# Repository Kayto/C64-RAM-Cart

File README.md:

# C64 RAM Cartridge

## Latest News

Please note this PCB remains untested so please review and understand the risk in proceeding.
I do hope to pick up in 2024 so watch this space.

## Background

C64 Cartridges were convenient and easy to use. Programs on cartridge loaded instantly. Typically cartridges used EPROMs (Erasable Programmable Read-Only Memories). The only downside of ROM was the inconvenience of making quick changes with the need for a seperate EPROM burner and an eraser. Contemporary articles note that EPROMS were relatively expensive at $25 each and the need for a burner and eraser equating to around $200.
As RAM became cheaper (at nearer $15 each) at the end of the 1980s, RAM based storage devices became more prevalent for the C64 with products such as the RAMLINK and GeoRAM cartridges finding use. Additional offerings were produced and hobbyist examples published such as the RAM cart presented here. Given the general developments in computing at this time, usage and adoption was rather limited by the availability of software towards the end of the 8 bit era. 

## Introduction
This C64 RAM cartridge is a recreation of the Super Luxus CMOS RAM Platine from the 64'er magazine dated March 1989. It provides 256Kb of battery backed RAM instead of the usual memory expansion provided by EPROMS. Put simply it acts as a RAM disc for the storage of data in conjunction with the program provided on an onboard EPROM. 

## Credit 

We should start with the credit, as this board was designed and created by J Schucht. The design files are offered for educational purposes only.
Thanks also due for [TEBL](https://github.com/tebl/C64-BlinkenDiag) and any associated credits for some of the KiCad items.

## Aims
My motivation for this recreation is as an electronics hobbyist and C64 fan - to improve KiCad, hardware workings and generally coding.

## The PCBs

KiCad, Schematics and Gerbers are provided. Renders of the boards are shown in the KiCad directory. Please review before making a commitment. No warranties or support are provided. As of this date the designs remain untested.

## The Code

The EPROM code containing the program for usage is avaiable on the associated 64'er disc. This is currently available from [archive.org](https://archive.org/download/64er_Magazin_89-03_1989_Markt_Technik_de_Side_A)

The control software (listing) is published in packed form, once the listing with the MSE has been entered and saved, the program "RAM-Platine.pac" must be loaded with "'8" and started with RUN. Two files are now created on the previously inserted floppy disk: "RAM PLATlNE 4.2" and "RAM RW $c 0000 4.2". 
The program "RAMPLATlNE4.2" is the control software to be burned into a 2764 EPROM. The second program allows you to read and write to the CMOS RAM without activating the control EPROM.

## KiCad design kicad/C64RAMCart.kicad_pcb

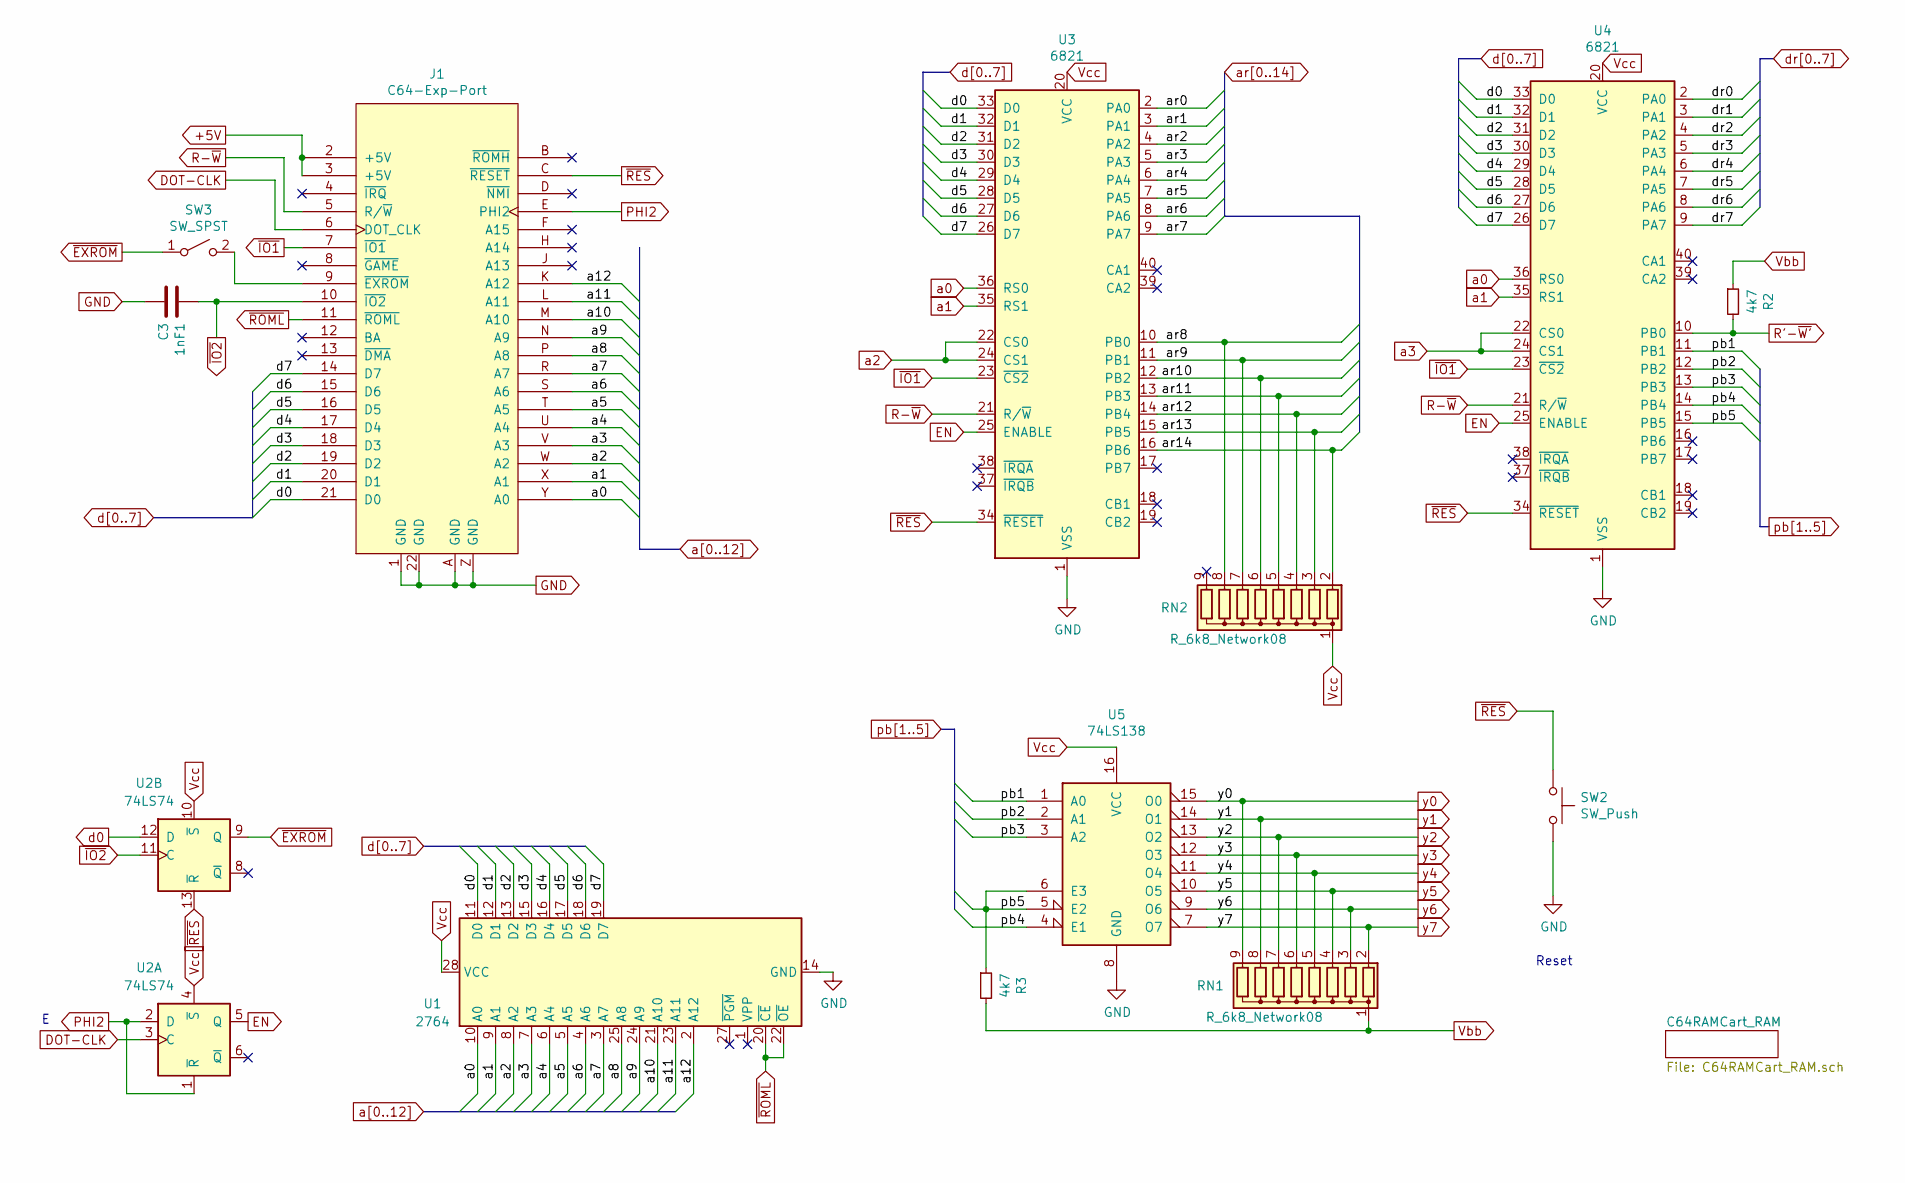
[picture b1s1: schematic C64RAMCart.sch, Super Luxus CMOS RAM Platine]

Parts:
1nF1: C3; C_Disc_D4.3mm_W1.9mm_P5.00mm
J1: C64-Exp-Port; C64_Expansion_Port
R2, R3: 4k7; R_Axial_DIN0207_L6.3mm_D2.5mm_P7.62mm_Horizontal
RN1, RN2: R_6k8_Network08; R_Array_SIP9
SW2: SW_Push; SW_PUSH_6mm_H7.3mm
SW3: SW_SPST; PinHeader_1x03_P2.54mm_Vertical
U1: 2764; DIP-28_W15.24mm_Socket
U2: 74LS74; DIP-14_W7.62mm_Socket
U3, U4: 6821; DIP-40_W15.24mm_Socket
U5: 74LS138; DIP-16_W7.62mm_Socket

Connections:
+5V: J1.2 (+5V), J1.3 (+5V), RN2.1 (common), U1.28 (VCC), U2.4 (~S), U2.10 (~S), U3.20 (VCC), U4.20 (VCC), U5.16 (VCC); also elsewhere on the board
BVcc: R2.1, R3.2, RN1.1 (common); also elsewhere on the board
DOT-CLK: J1.6 (DOT_CLK), U2.3 (C)
EN: U2.5 (Q), U3.25 (ENABLE), U4.25 (ENABLE)
GND: 1nF1.2, J1.1 (GND), J1.22 (GND), J1.A (GND), J1.Z (GND), SW2.2, U1.14 (GND), U3.1 (VSS), U4.1 (VSS), U5.8 (GND); also elsewhere on the board
unnamed: J1.9 (~EXROM), SW3.2 (B)
PHI2: J1.E (PHI2), U2.1 (~R), U2.2 (D)
R'-~W': R2.2, U4.10 (PB0); also elsewhere on the board
R-~W: J1.5 (R/~W), U3.21 (R/~W), U4.21 (R/~W)
a0: J1.Y (A0), U1.10 (A0), U3.36 (RS0), U4.36 (RS0)
a1: J1.X (A1), U1.9 (A1), U3.35 (RS1), U4.35 (RS1)
a2: J1.W (A2), U1.8 (A2), U3.22 (CS0), U3.24 (CS1)
a3: J1.V (A3), U1.7 (A3), U4.22 (CS0), U4.24 (CS1)
a4: J1.U (A4), U1.6 (A4)
a5: J1.T (A5), U1.5 (A5)
a6: J1.S (A6), U1.4 (A6)
a7: J1.R (A7), U1.3 (A7)
a8: J1.P (A8), U1.25 (A8)
a9: J1.N (A9), U1.24 (A9)
a10: J1.M (A10), U1.21 (A10)
a11: J1.L (A11), U1.23 (A11)
a12: J1.K (A12), U1.2 (A12)
ar0: U3.2 (PA0); also elsewhere on the board
ar1: U3.3 (PA1); also elsewhere on the board
ar2: U3.4 (PA2); also elsewhere on the board
ar3: U3.5 (PA3); also elsewhere on the board
ar4: U3.6 (PA4); also elsewhere on the board
ar5: U3.7 (PA5); also elsewhere on the board
ar6: U3.8 (PA6); also elsewhere on the board
ar7: U3.9 (PA7); also elsewhere on the board
ar8: RN2.8 (R7), U3.10 (PB0); also elsewhere on the board
ar9: RN2.7 (R6), U3.11 (PB1); also elsewhere on the board
ar10: RN2.6 (R5), U3.12 (PB2); also elsewhere on the board
ar11: RN2.5 (R4), U3.13 (PB3); also elsewhere on the board
ar12: RN2.4 (R3), U3.14 (PB4); also elsewhere on the board
ar13: RN2.3 (R2), U3.15 (PB5); also elsewhere on the board
ar14: RN2.2 (R1), U3.16 (PB6); also elsewhere on the board
d0: J1.21 (D0), U1.11 (D0), U2.12 (D), U3.33 (D0), U4.33 (D0)
d1: J1.20 (D1), U1.12 (D1), U3.32 (D1), U4.32 (D1)
d2: J1.19 (D2), U1.13 (D2), U3.31 (D2), U4.31 (D2)
d3: J1.18 (D3), U1.15 (D3), U3.30 (D3), U4.30 (D3)
d4: J1.17 (D4), U1.16 (D4), U3.29 (D4), U4.29 (D4)
d5: J1.16 (D5), U1.17 (D5), U3.28 (D5), U4.28 (D5)
d6: J1.15 (D6), U1.18 (D6), U3.27 (D6), U4.27 (D6)
d7: J1.14 (D7), U1.19 (D7), U3.26 (D7), U4.26 (D7)
dr0: U4.2 (PA0); also elsewhere on the board
dr1: U4.3 (PA1); also elsewhere on the board
dr2: U4.4 (PA2); also elsewhere on the board
dr3: U4.5 (PA3); also elsewhere on the board
dr4: U4.6 (PA4); also elsewhere on the board
dr5: U4.7 (PA5); also elsewhere on the board
dr6: U4.8 (PA6); also elsewhere on the board
dr7: U4.9 (PA7); also elsewhere on the board
pb1: U4.11 (PB1), U5.1 (A0)
pb2: U4.12 (PB2), U5.2 (A1)
pb3: U4.13 (PB3), U5.3 (A2)
pb4: U4.14 (PB4), U5.4 (E1)
pb5: R3.1, U4.15 (PB5), U5.5 (E2), U5.6 (E3)
y0: RN1.9 (R8), U5.15 (O0); also elsewhere on the board
y1: RN1.8 (R7), U5.14 (O1); also elsewhere on the board
y2: RN1.7 (R6), U5.13 (O2); also elsewhere on the board
y3: RN1.6 (R5), U5.12 (O3); also elsewhere on the board
y4: RN1.5 (R4), U5.11 (O4); also elsewhere on the board
y5: RN1.4 (R3), U5.10 (O5); also elsewhere on the board
y6: RN1.3 (R2), U5.9 (O6); also elsewhere on the board
y7: RN1.2 (R1), U5.7 (O7); also elsewhere on the board
~EXROM: SW3.1 (A), U2.9 (Q)
~IO1: J1.7 (~IO1), U3.23 (~CS2), U4.23 (~CS2)
~IO2: 1nF1.1, J1.10 (~IO2), U2.11 (C)
~RES: J1.C (~RESET), SW2.1, U2.13 (~R), U3.34 (~RESET), U4.34 (~RESET)
~ROML: J1.11 (~ROML), U1.20 (~CE), U1.22 (~OE)

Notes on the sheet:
Reset

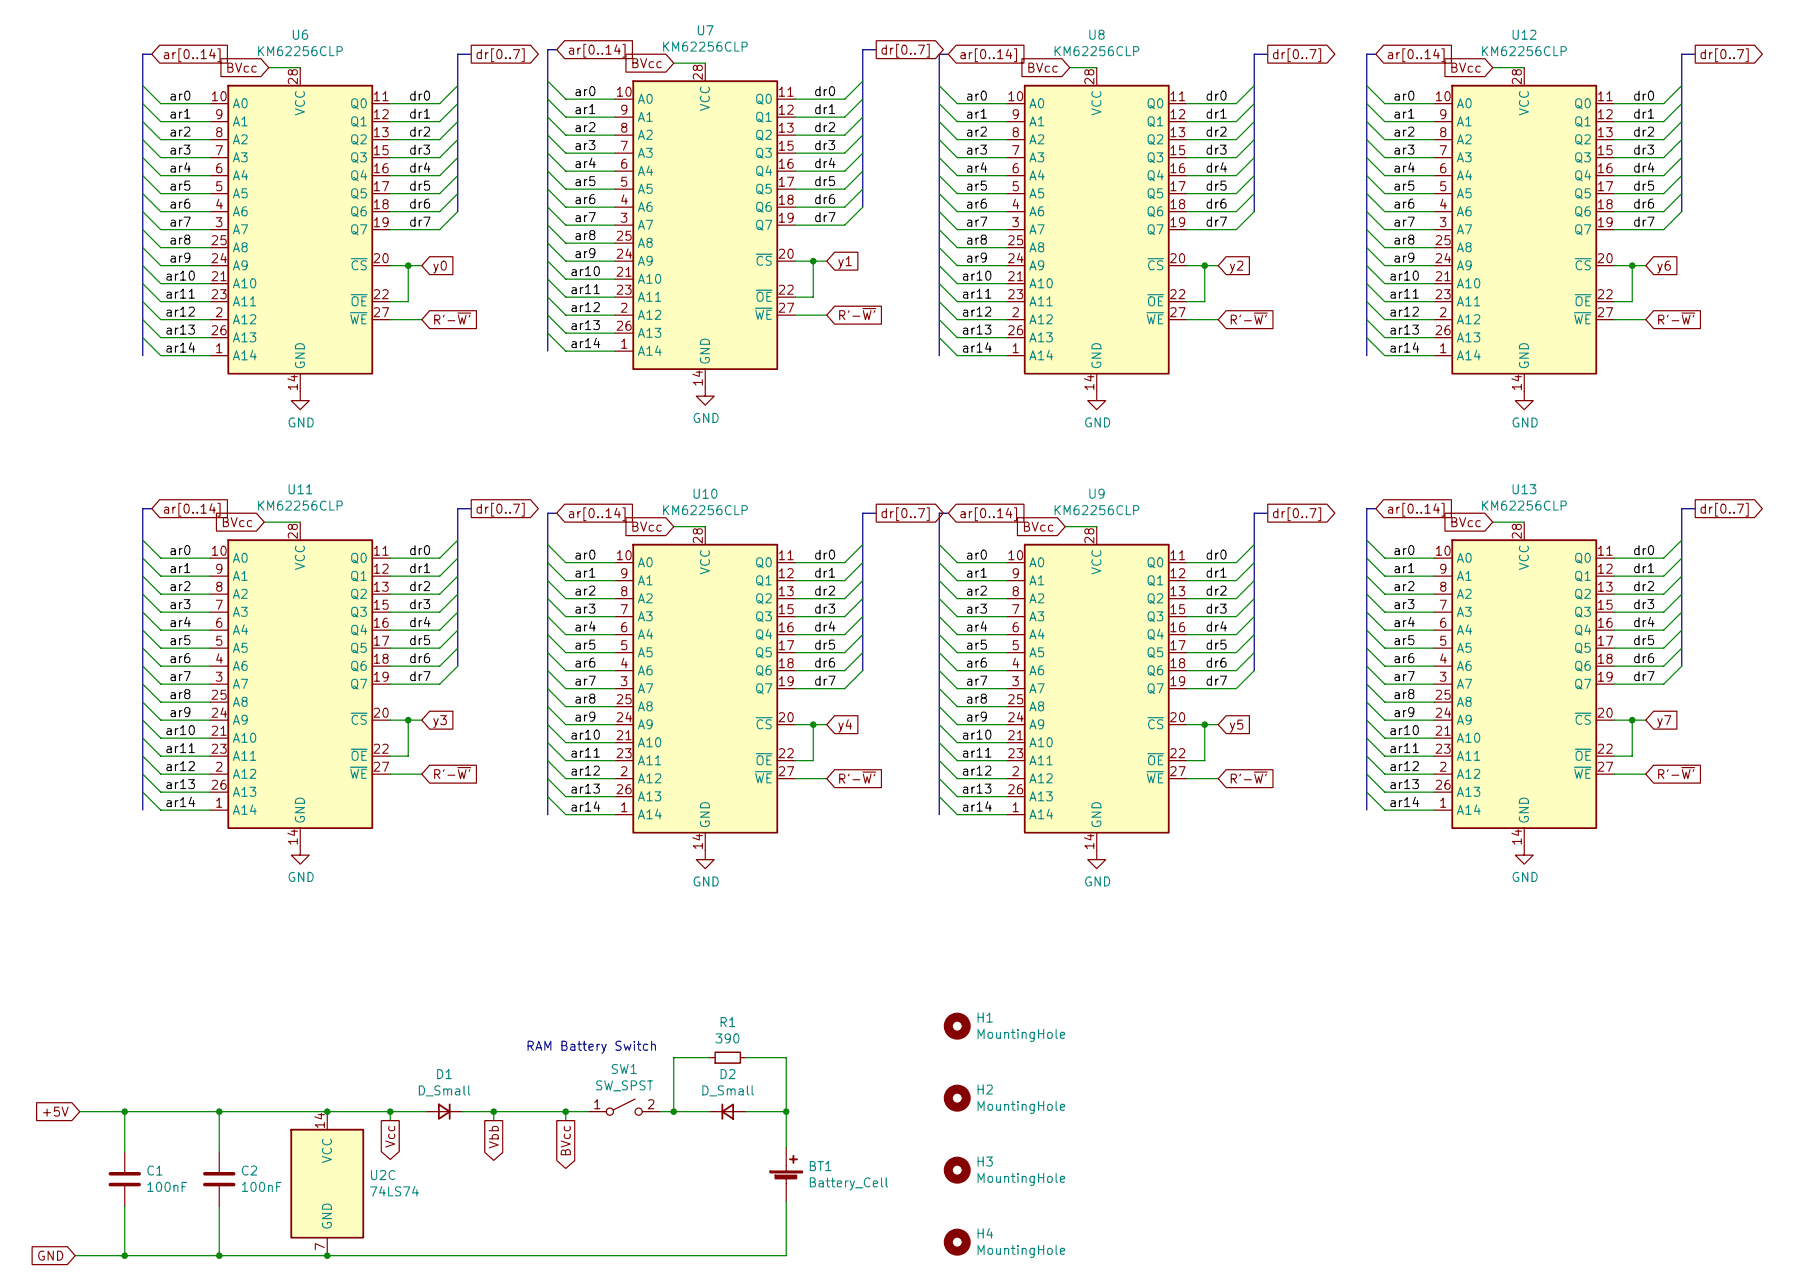
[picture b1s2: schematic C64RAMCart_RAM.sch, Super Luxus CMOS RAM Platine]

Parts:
BT1: Battery_Cell; BatteryHolder_Keystone_103_1x20mm
C1, C2: 100nF; C_Disc_D4.3mm_W1.9mm_P5.00mm
D1, D2: D_Small; D_DO-15_P10.16mm_Horizontal
H1, H2, H3, H4: MountingHole; M3_pin
R1: 390; R_Axial_DIN0207_L6.3mm_D2.5mm_P7.62mm_Horizontal
SW1: SW_SPST; PinHeader_1x03_P2.54mm_Vertical
U2: 74LS74; DIP-14_W7.62mm_Socket
U6, U7, U8, U9, U10, U11, U12, U13: KM62256CLP; DIP-28_W15.24mm_Socket

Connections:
+5V: C1.1, C2.1, D1.2 (A), U2.14 (VCC); also elsewhere on the board
BVcc: D1.1 (K), SW1.1 (A), U6.28 (VCC), U7.28 (VCC), U8.28 (VCC), U9.28 (VCC), U10.28 (VCC), U11.28 (VCC), U12.28 (VCC), U13.28 (VCC); also elsewhere on the board
GND: BT1.2 (-), C1.2, C2.2, U2.7 (GND), U6.14 (GND), U7.14 (GND), U8.14 (GND), U9.14 (GND), U10.14 (GND), U11.14 (GND), U12.14 (GND), U13.14 (GND); also elsewhere on the board
unnamed: BT1.1 (+), D2.2 (A), R1.2
unnamed: D2.1 (K), R1.1, SW1.2 (B)
R'-~W': U6.27 (~WE), U7.27 (~WE), U8.27 (~WE), U9.27 (~WE), U10.27 (~WE), U11.27 (~WE), U12.27 (~WE), U13.27 (~WE); also elsewhere on the board
ar0: U6.10 (A0), U7.10 (A0), U8.10 (A0), U9.10 (A0), U10.10 (A0), U11.10 (A0), U12.10 (A0), U13.10 (A0); also elsewhere on the board
ar1: U6.9 (A1), U7.9 (A1), U8.9 (A1), U9.9 (A1), U10.9 (A1), U11.9 (A1), U12.9 (A1), U13.9 (A1); also elsewhere on the board
ar2: U6.8 (A2), U7.8 (A2), U8.8 (A2), U9.8 (A2), U10.8 (A2), U11.8 (A2), U12.8 (A2), U13.8 (A2); also elsewhere on the board
ar3: U6.7 (A3), U7.7 (A3), U8.7 (A3), U9.7 (A3), U10.7 (A3), U11.7 (A3), U12.7 (A3), U13.7 (A3); also elsewhere on the board
ar4: U6.6 (A4), U7.6 (A4), U8.6 (A4), U9.6 (A4), U10.6 (A4), U11.6 (A4), U12.6 (A4), U13.6 (A4); also elsewhere on the board
ar5: U6.5 (A5), U7.5 (A5), U8.5 (A5), U9.5 (A5), U10.5 (A5), U11.5 (A5), U12.5 (A5), U13.5 (A5); also elsewhere on the board
ar6: U6.4 (A6), U7.4 (A6), U8.4 (A6), U9.4 (A6), U10.4 (A6), U11.4 (A6), U12.4 (A6), U13.4 (A6); also elsewhere on the board
ar7: U6.3 (A7), U7.3 (A7), U8.3 (A7), U9.3 (A7), U10.3 (A7), U11.3 (A7), U12.3 (A7), U13.3 (A7); also elsewhere on the board
ar8: U6.25 (A8), U7.25 (A8), U8.25 (A8), U9.25 (A8), U10.25 (A8), U11.25 (A8), U12.25 (A8), U13.25 (A8); also elsewhere on the board
ar9: U6.24 (A9), U7.24 (A9), U8.24 (A9), U9.24 (A9), U10.24 (A9), U11.24 (A9), U12.24 (A9), U13.24 (A9); also elsewhere on the board
ar10: U6.21 (A10), U7.21 (A10), U8.21 (A10), U9.21 (A10), U10.21 (A10), U11.21 (A10), U12.21 (A10), U13.21 (A10); also elsewhere on the board
ar11: U6.23 (A11), U7.23 (A11), U8.23 (A11), U9.23 (A11), U10.23 (A11), U11.23 (A11), U12.23 (A11), U13.23 (A11); also elsewhere on the board
ar12: U6.2 (A12), U7.2 (A12), U8.2 (A12), U9.2 (A12), U10.2 (A12), U11.2 (A12), U12.2 (A12), U13.2 (A12); also elsewhere on the board
ar13: U6.26 (A13), U7.26 (A13), U8.26 (A13), U9.26 (A13), U10.26 (A13), U11.26 (A13), U12.26 (A13), U13.26 (A13); also elsewhere on the board
ar14: U6.1 (A14), U7.1 (A14), U8.1 (A14), U9.1 (A14), U10.1 (A14), U11.1 (A14), U12.1 (A14), U13.1 (A14); also elsewhere on the board
dr0: U6.11 (Q0), U7.11 (Q0), U8.11 (Q0), U9.11 (Q0), U10.11 (Q0), U11.11 (Q0), U12.11 (Q0), U13.11 (Q0); also elsewhere on the board
dr1: U6.12 (Q1), U7.12 (Q1), U8.12 (Q1), U9.12 (Q1), U10.12 (Q1), U11.12 (Q1), U12.12 (Q1), U13.12 (Q1); also elsewhere on the board
dr2: U6.13 (Q2), U7.13 (Q2), U8.13 (Q2), U9.13 (Q2), U10.13 (Q2), U11.13 (Q2), U12.13 (Q2), U13.13 (Q2); also elsewhere on the board
dr3: U6.15 (Q3), U7.15 (Q3), U8.15 (Q3), U9.15 (Q3), U10.15 (Q3), U11.15 (Q3), U12.15 (Q3), U13.15 (Q3); also elsewhere on the board
dr4: U6.16 (Q4), U7.16 (Q4), U8.16 (Q4), U9.16 (Q4), U10.16 (Q4), U11.16 (Q4), U12.16 (Q4), U13.16 (Q4); also elsewhere on the board
dr5: U6.17 (Q5), U7.17 (Q5), U8.17 (Q5), U9.17 (Q5), U10.17 (Q5), U11.17 (Q5), U12.17 (Q5), U13.17 (Q5); also elsewhere on the board
dr6: U6.18 (Q6), U7.18 (Q6), U8.18 (Q6), U9.18 (Q6), U10.18 (Q6), U11.18 (Q6), U12.18 (Q6), U13.18 (Q6); also elsewhere on the board
dr7: U6.19 (Q7), U7.19 (Q7), U8.19 (Q7), U9.19 (Q7), U10.19 (Q7), U11.19 (Q7), U12.19 (Q7), U13.19 (Q7); also elsewhere on the board
y0: U6.20 (~CS), U6.22 (~OE); also elsewhere on the board
y1: U7.20 (~CS), U7.22 (~OE); also elsewhere on the board
y2: U8.20 (~CS), U8.22 (~OE); also elsewhere on the board
y3: U11.20 (~CS), U11.22 (~OE); also elsewhere on the board
y4: U10.20 (~CS), U10.22 (~OE); also elsewhere on the board
y5: U9.20 (~CS), U9.22 (~OE); also elsewhere on the board
y6: U12.20 (~CS), U12.22 (~OE); also elsewhere on the board
y7: U13.20 (~CS), U13.22 (~OE); also elsewhere on the board

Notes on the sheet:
RAM Battery Switch

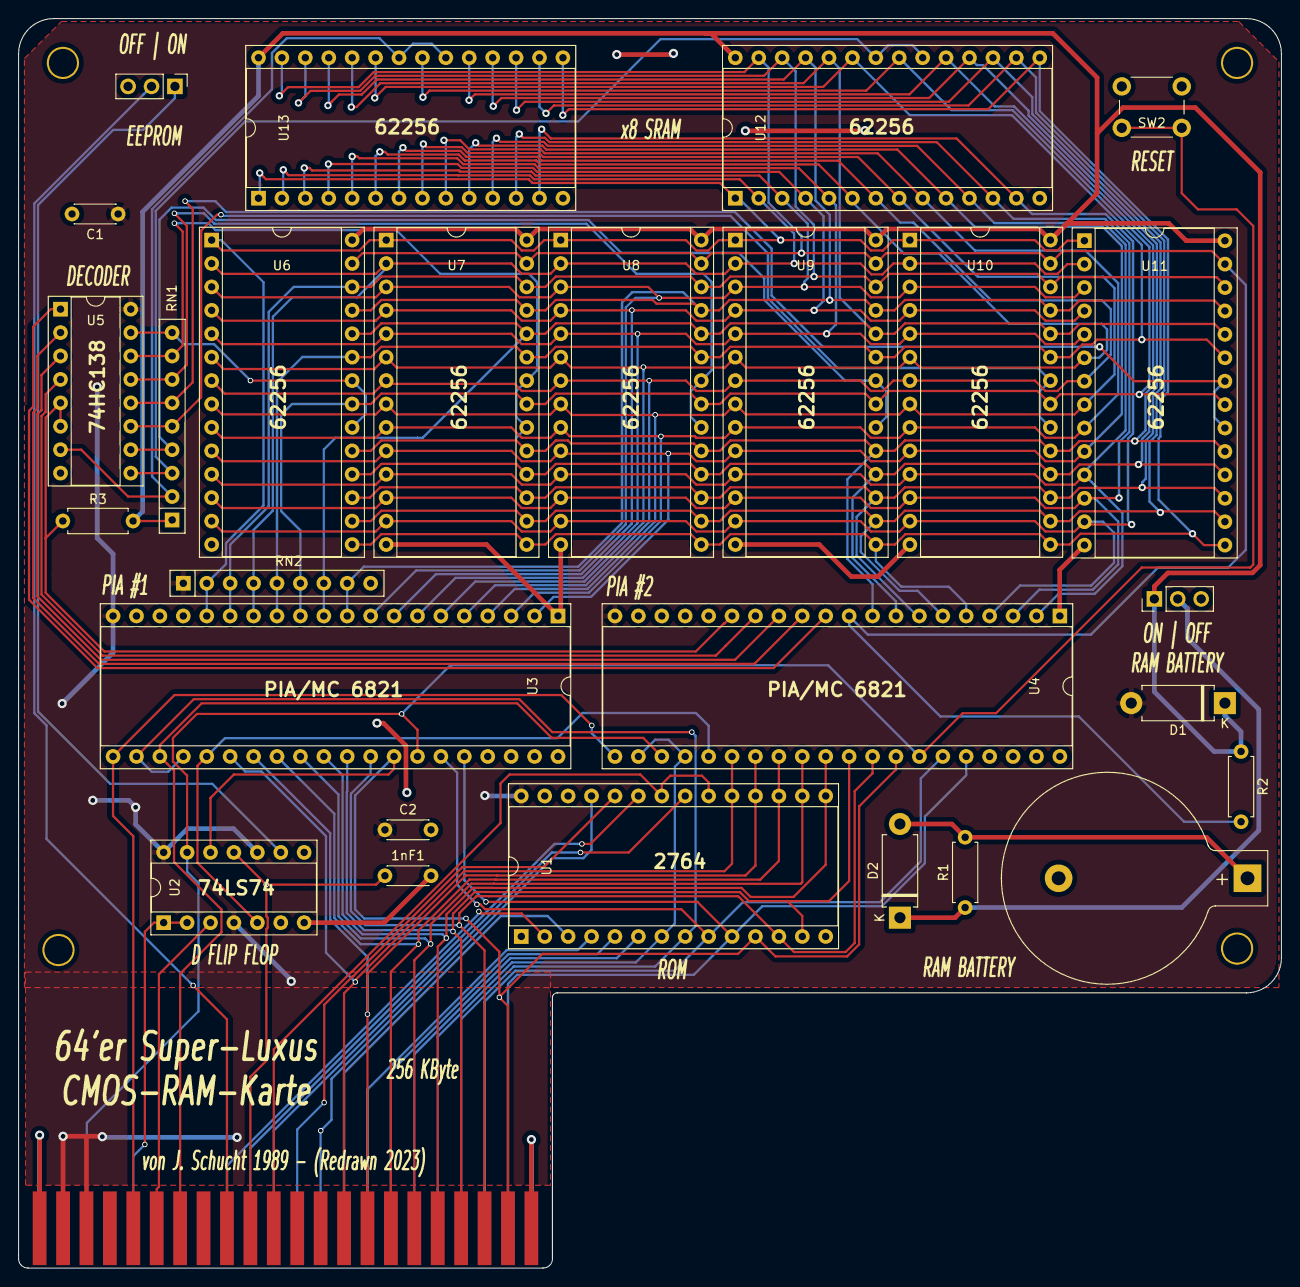
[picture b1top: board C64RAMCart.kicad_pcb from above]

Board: 2 copper layers, 137.0 x 135.5 mm, 32 parts (0 on the bottom side), 73 nets.

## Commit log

2023-04-19 Gerbers and Schematic
2023-04-19 image added
2023-04-22 RES fixed
2023-04-24 RES correction
2023-04-24 Label Updates
2023-04-24 PCB and Schematic tidy
2023-04-24 Remaining SRAM added
